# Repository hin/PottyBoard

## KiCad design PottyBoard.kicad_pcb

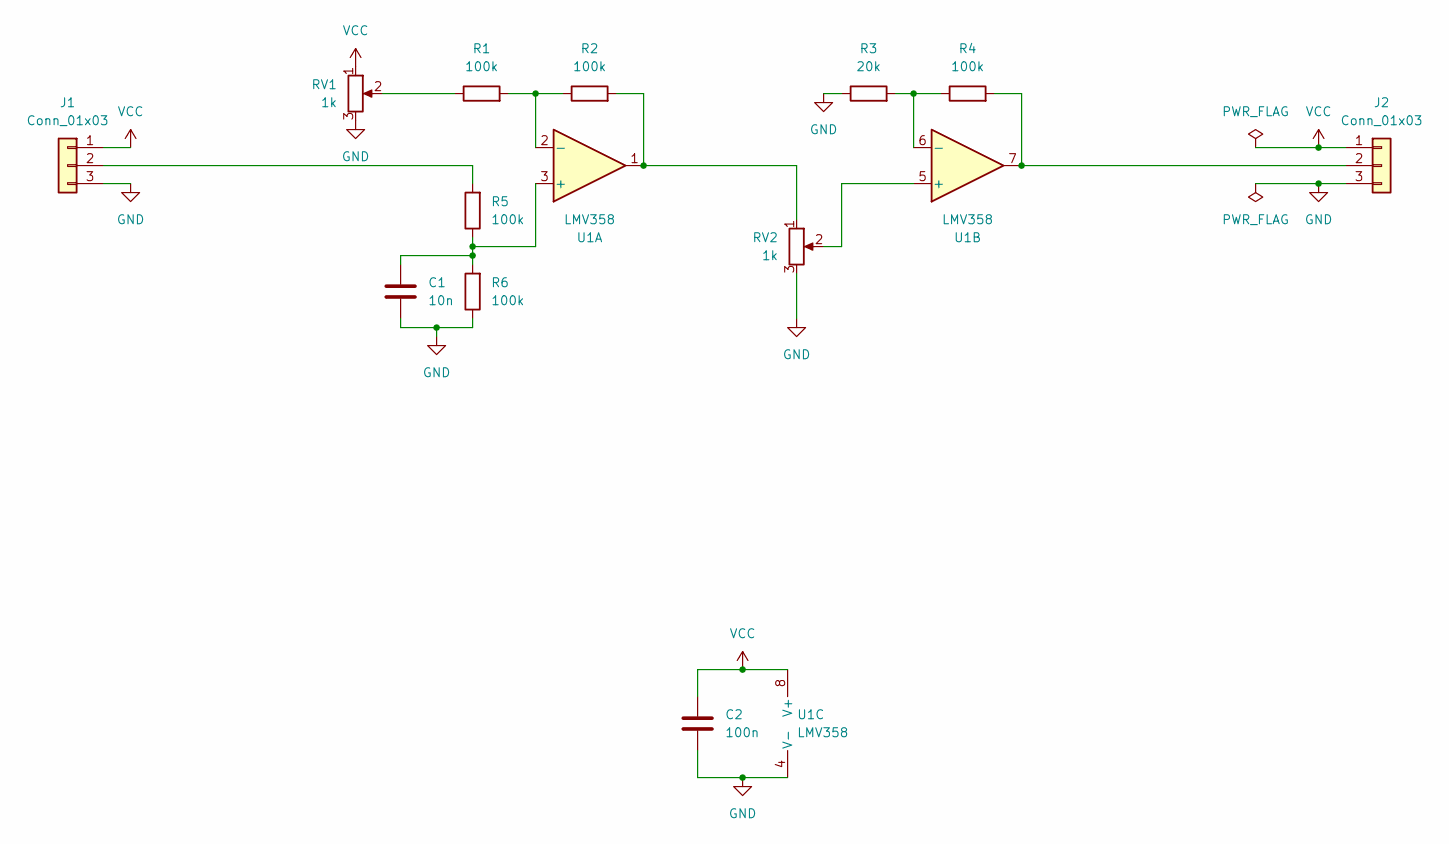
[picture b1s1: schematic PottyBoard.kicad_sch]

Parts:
C1: 10n; C_0402_1005Metric
C2: 100n; C_0402_1005Metric
J1, J2: Conn_01x03; PinHeader_1x03_P2.54mm_Vertical
R1, R2, R4, R5, R6: 100k; R_0402_1005Metric
R3: 20k; R_0402_1005Metric
RV1, RV2: 1k; Potentiometer_Bourns_TC33X_Vertical; LCSC C719174
U1: LMV358; SOT-23-8; LCSC C2869788

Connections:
GND: C1.2, C2.2, J1.3, J2.3, R3.1, R6.1, RV1.3, RV2.3, U1.4 (V-)
unnamed: J1.2, R5.2
unnamed: J2.2, R4.2, U1.7
unnamed: R1.1, RV1.2
unnamed: R2.2, RV2.1, U1.1
unnamed: C1.1, R5.1, R6.2, U1.3 (+)
unnamed: R1.2, R2.1, U1.2 (-)
unnamed: RV2.2, U1.5 (+)
unnamed: R3.2, R4.1, U1.6 (-)
VCC: C2.1, J1.1, J2.1, RV1.1, U1.8 (V+)

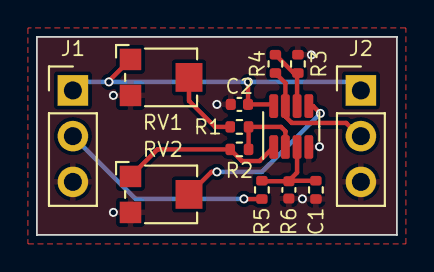
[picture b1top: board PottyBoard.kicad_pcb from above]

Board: 4 copper layers, 20.0 x 11.0 mm, 13 parts (0 on the bottom side), 10 nets.

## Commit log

2024-02-09 First version of PottyBoard
2024-02-09 Add footprint for filtering capacitor
2024-02-13 PCB layout
2024-02-26 Finish first version
